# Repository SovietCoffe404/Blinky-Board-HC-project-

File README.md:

# Blinky-Board-HC-project-
This is another guided project for HC Stasis

I've only used KiCAD for this project so I will leave a link for download in case you wanna do it too!

https://www.kicad.org/download/

As well here are my files if you wanna modify or just take a look to them.

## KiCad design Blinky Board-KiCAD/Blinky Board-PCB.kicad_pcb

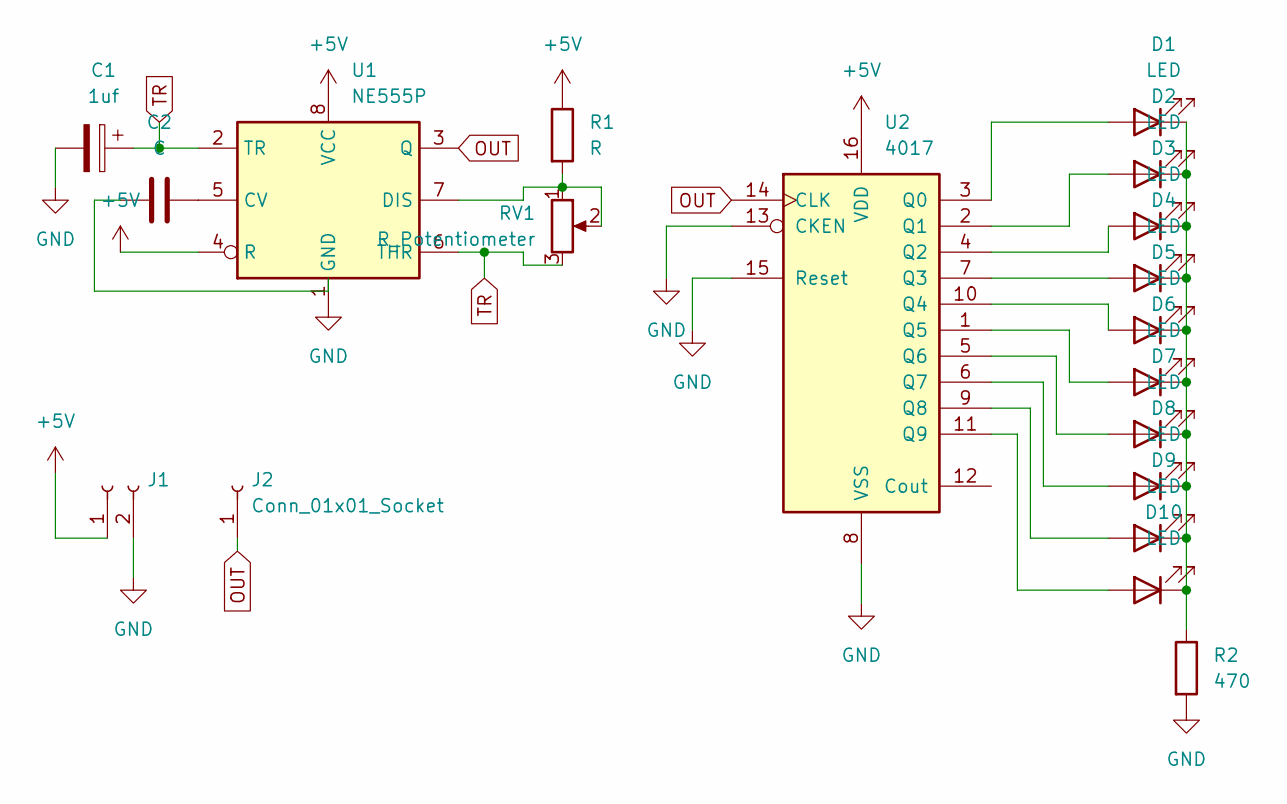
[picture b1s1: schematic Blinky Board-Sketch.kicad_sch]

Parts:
C1: 1uf; CP_Radial_D5.0mm_P2.00mm
C2: C; C_Disc_D7.0mm_W2.5mm_P5.00mm
D1, D2, D3, D4, D5, D6, D7, D8, D9, D10: LED; LED_D3.0mm
J1: PinHeader_2x01_P2.54mm_Horizontal
J2: Conn_01x01_Socket; PinHeader_1x01_P2.54mm_Horizontal
R1: R; R_Axial_DIN0207_L6.3mm_D2.5mm_P2.54mm_Vertical
R2: 470; R_Axial_DIN0207_L6.3mm_D2.5mm_P2.54mm_Vertical
RV1: R_Potentiometer; Potentiometer_Vishay_T93YA_Vertical
U1: NE555P; DIP-8_W7.62mm
U2: 4017; N16

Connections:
+5V: J1.1, R1.1, U1.4 (R), U1.8 (VCC), U2.16 (VDD)
GND: C1.2, J1.2, R2.2, U1.1 (GND), U2.8 (VSS), U2.13 (CKEN), U2.15 (Reset)
unnamed: D1.2 (A), U2.3 (Q0)
unnamed: D1.1 (K), D2.1 (K), D3.1 (K), D4.1 (K), D5.1 (K), D6.1 (K), D7.1 (K), D8.1 (K), D9.1 (K), D10.1 (K), R2.1
unnamed: D2.2 (A), U2.2 (Q1)
unnamed: D3.2 (A), U2.4 (Q2)
unnamed: D4.2 (A), U2.7 (Q3)
unnamed: D5.2 (A), U2.10 (Q4)
unnamed: D6.2 (A), U2.1 (Q5)
unnamed: D7.2 (A), U2.5 (Q6)
unnamed: D8.2 (A), U2.6 (Q7)
unnamed: D9.2 (A), U2.9 (Q8)
unnamed: D10.2 (A), U2.11 (Q9)
unnamed: C2.2, U1.5 (CV)
unnamed: R1.2, RV1.1, RV1.2, U1.7 (DIS)
OUT: J2.1, U1.3 (Q), U2.14 (CLK)
TR: C1.1, RV1.3, U1.2 (TR), U1.6 (THR)

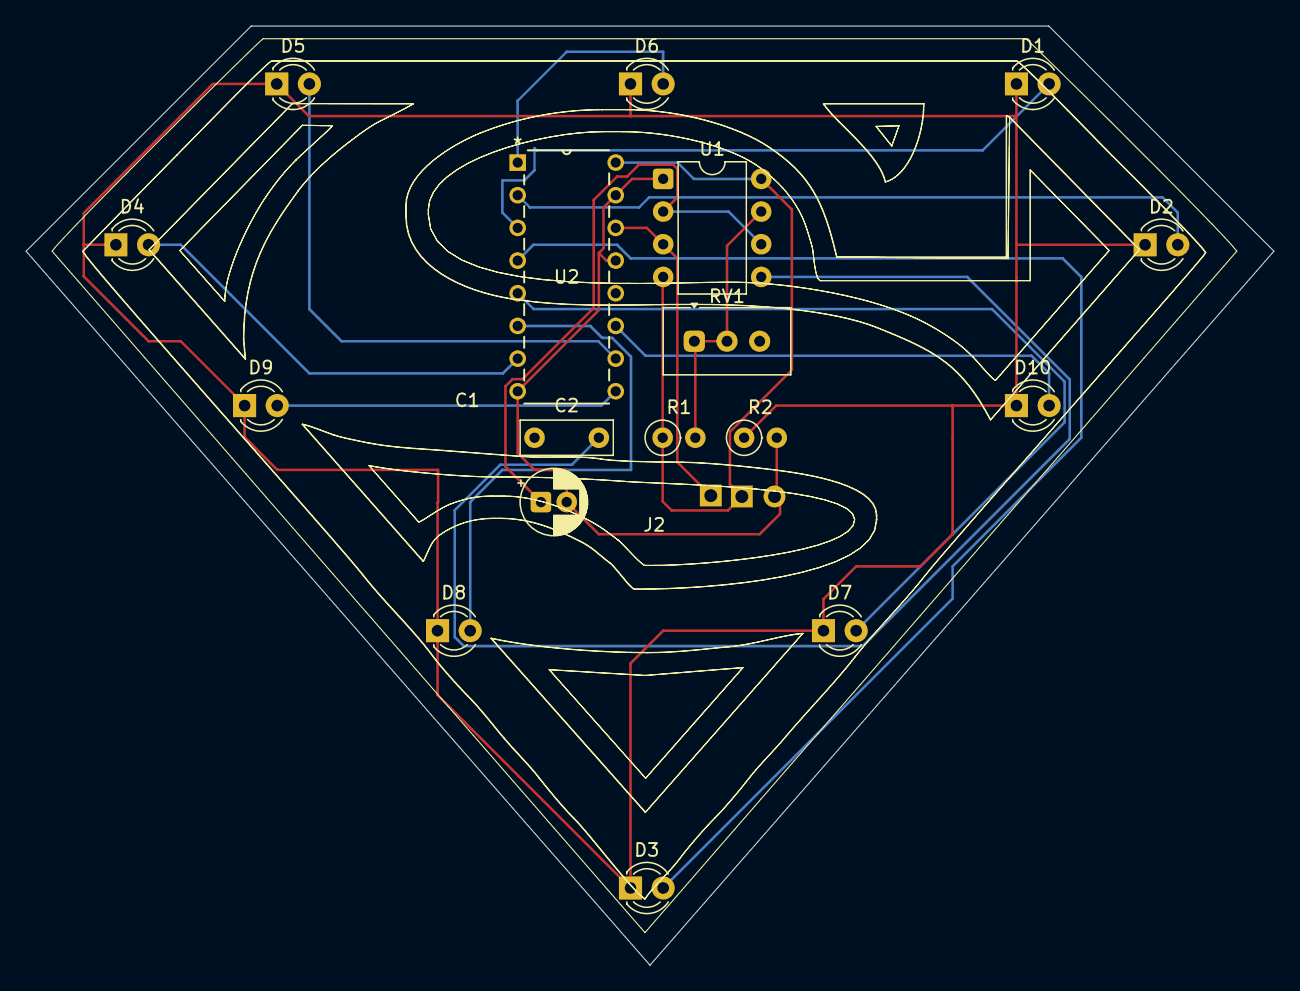
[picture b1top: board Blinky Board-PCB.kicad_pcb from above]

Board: 2 copper layers, 97.0 x 73.0 mm, 19 parts (0 on the bottom side), 17 nets.

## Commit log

2026-04-27 Add additional screenshot to README
    Added a new screenshot to the README.
